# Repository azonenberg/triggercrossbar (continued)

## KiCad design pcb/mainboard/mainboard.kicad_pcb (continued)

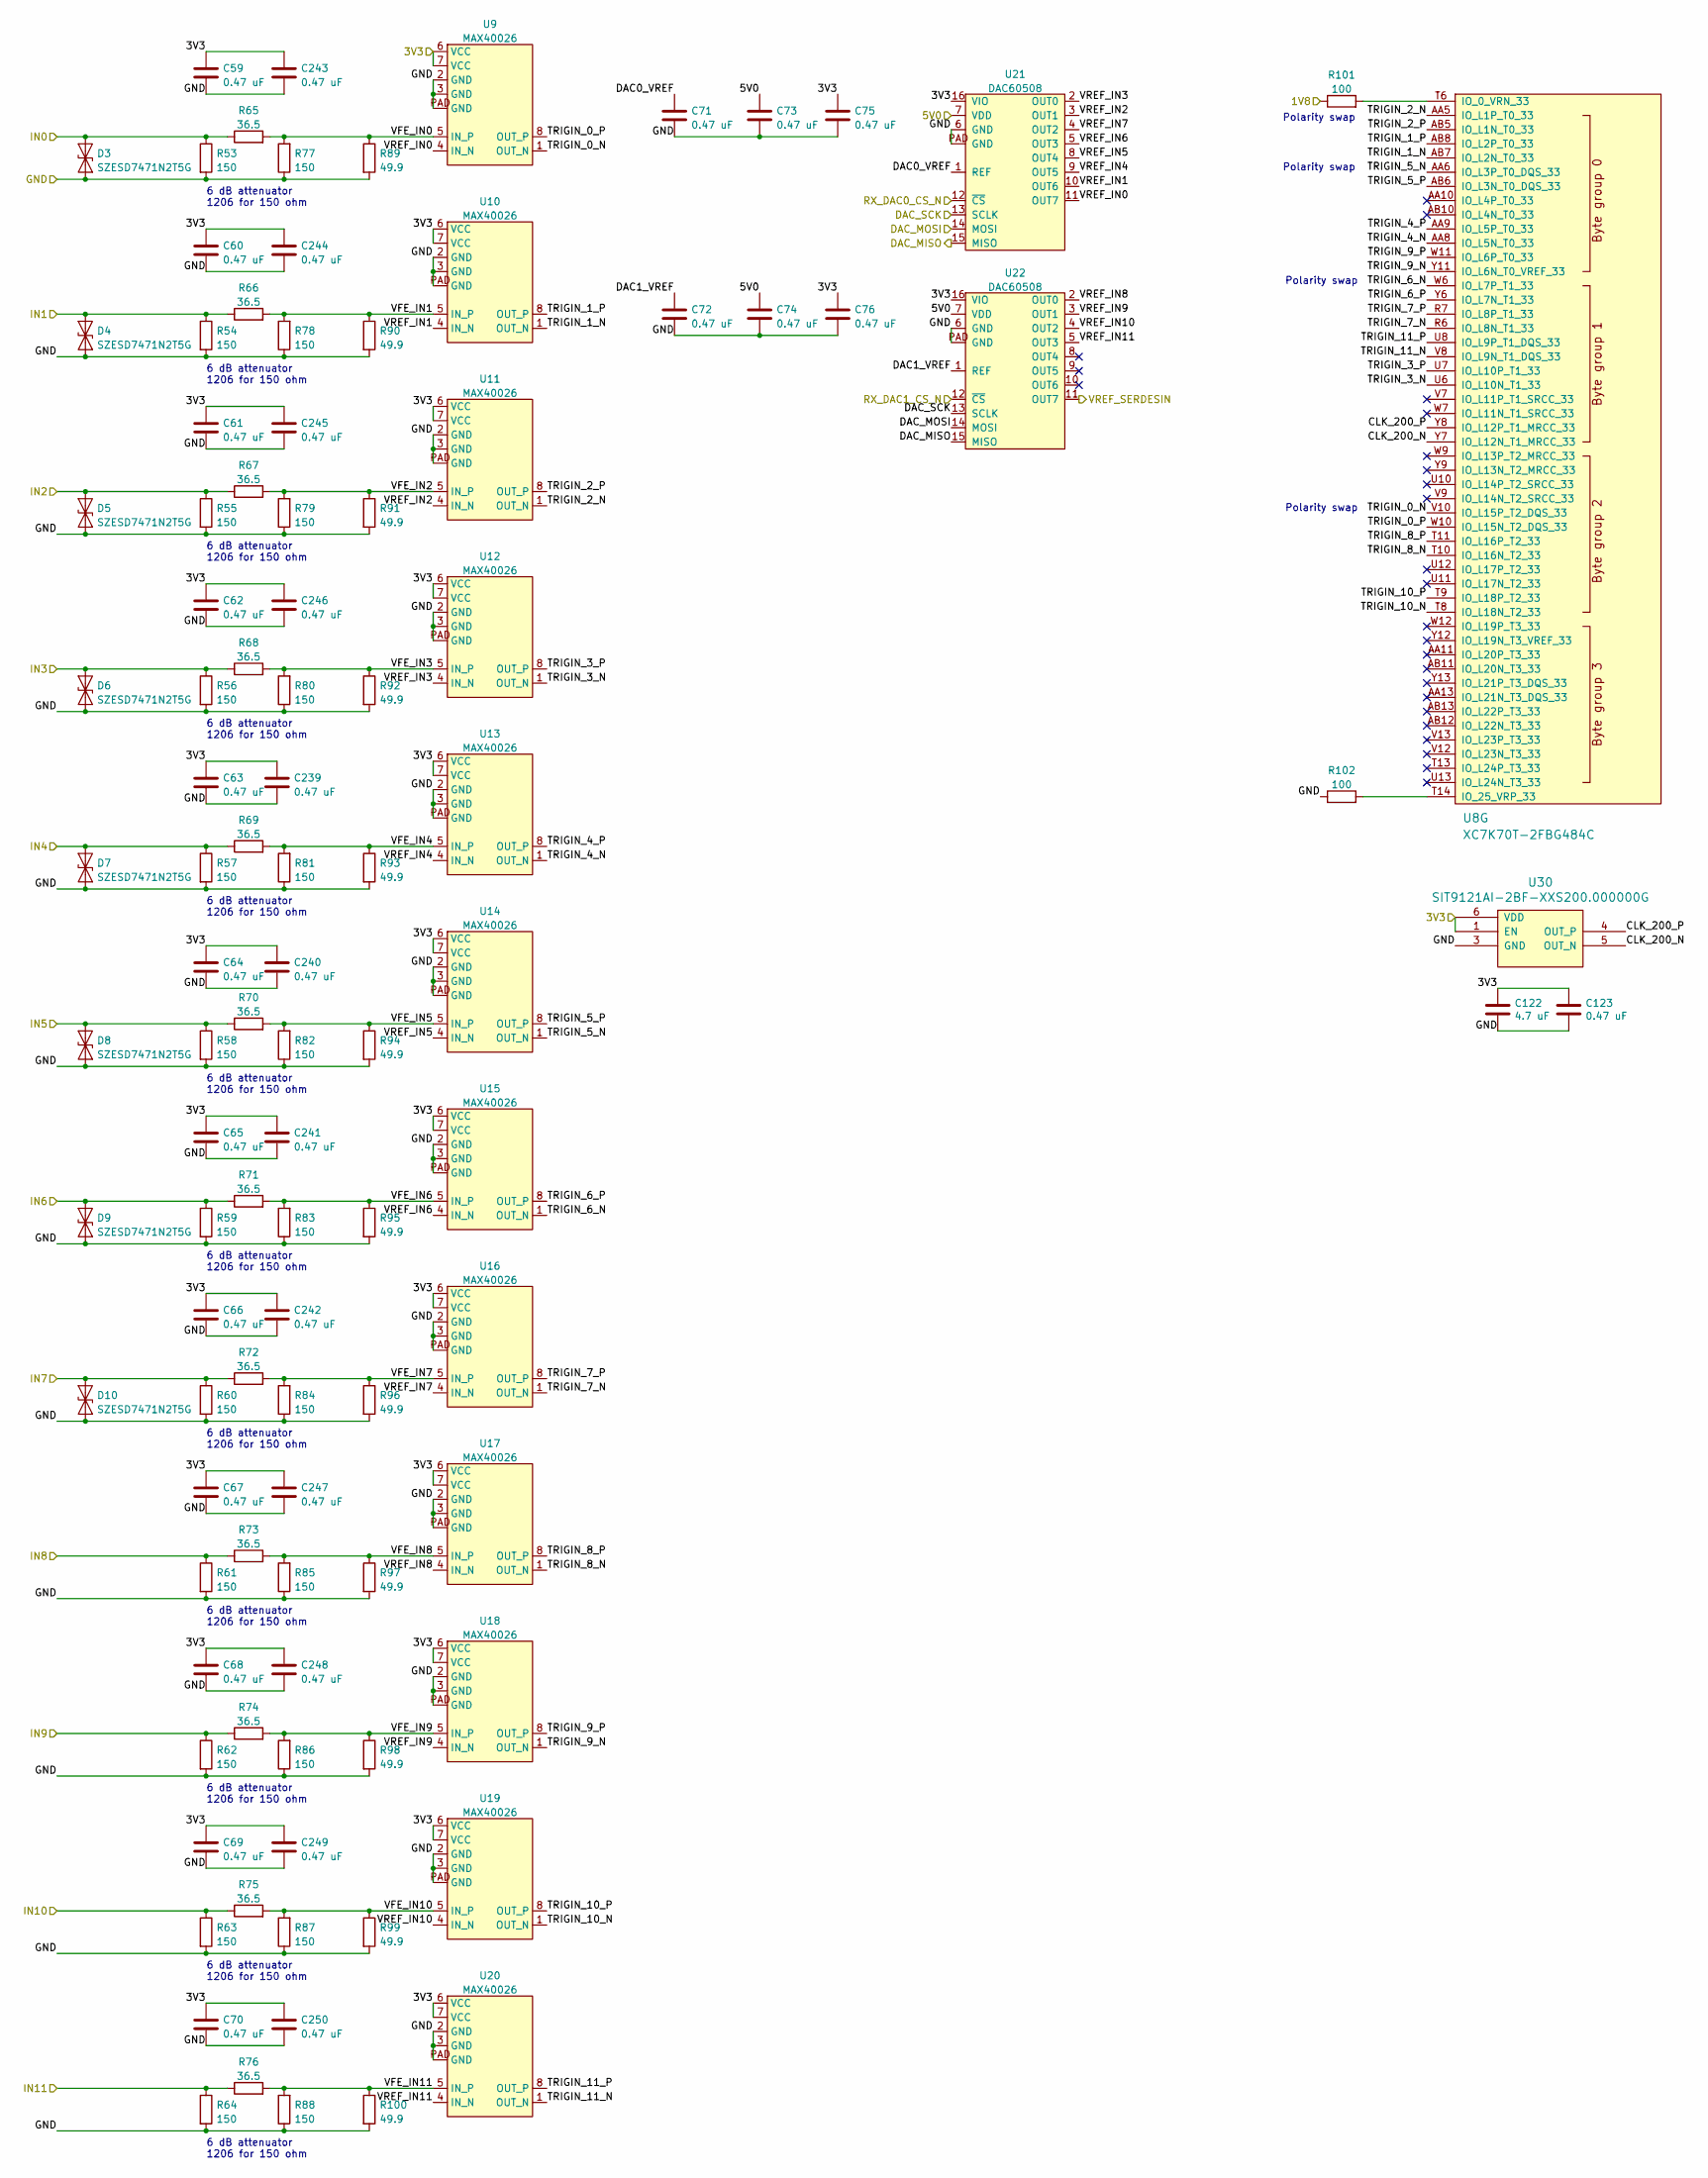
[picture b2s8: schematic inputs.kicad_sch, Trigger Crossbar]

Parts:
C59, C60, C61, C62, C63, C64, C65, C66, C67, C68, C69, C70, C71, C72, C73, C74, C75, C76, C123, C239, C240, C241, C242, C243, C244, C245, C246, C247, C248, C249, C250: 0.47 uF; EIA_0402_CAP_NOSILK
C122: 4.7 uF; EIA_0603_CAP_NOSILK
D3, D4, D5, D6, D7, D8, D9, D10: SZESD7471N2T5G; SOD882
R53, R54, R55, R56, R57, R58, R59, R60, R61, R62, R63, R64, R77, R78, R79, R80, R81, R82, R83, R84, R85, R86, R87, R88: 150; EIA_1206_CAP_NOSILK
R65, R66, R67, R68, R69, R70, R71, R72, R73, R74, R75, R76: 36.5; EIA_0402_RES_NOSILK
R89, R90, R91, R92, R93, R94, R95, R96, R97, R98, R99, R100: 49.9; EIA_0402_RES_NOSILK
R101, R102: 100; EIA_0402_RES_NOSILK
U8: XC7K70T-2FBG484C; BGA_484_22x22_FULLARRAY_1MM
U9, U10, U11, U12, U13, U14, U15, U16, U17, U18, U19, U20: MAX40026; DFN_8_0.5MM_2x2MM
U21, U22: DAC60508; QFN_16_0.5MM_3x3MM
U30: SIT9121AI-2BF-XXS200.000000G; OSCILLATOR_LVDS_3.2x2.5

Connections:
/3V3: C59.1, C60.1, C61.1, C62.1, C63.1, C64.1, C65.1, C66.1, C67.1, C68.1, C69.1, C70.1, C75.1, C76.1, C122.1, C123.1, C239.1, C240.1, C241.1, C242.1, C243.1, C244.1, C245.1, C246.1, C247.1, C248.1, C249.1, C250.1, U9.6 (VCC), U9.7 (VCC), U10.6 (VCC), U10.7 (VCC), U11.6 (VCC), U11.7 (VCC), U12.6 (VCC), U12.7 (VCC), U13.6 (VCC), U13.7 (VCC), U14.6 (VCC), U14.7 (VCC), U15.6 (VCC), U15.7 (VCC), U16.6 (VCC), U16.7 (VCC), U17.6 (VCC), U17.7 (VCC), U18.6 (VCC), U18.7 (VCC), U19.6 (VCC), U19.7 (VCC), U20.6 (VCC), U20.7 (VCC), U21.16 (VIO), U22.16 (VIO), U30.1 (EN), U30.6 (VDD); also elsewhere on the board
/5V0: C73.1, C74.1, U21.7 (VDD), U22.7 (VDD); also elsewhere on the board
/Connectors/IN0: D3.2 (A2), R53.1, R65.1; also elsewhere on the board
/Connectors/IN1: D4.2 (A2), R54.1, R66.1; also elsewhere on the board
/Connectors/IN2: D5.2 (A2), R55.1, R67.1; also elsewhere on the board
/Connectors/IN3: D6.2 (A2), R56.1, R68.1; also elsewhere on the board
/Connectors/IN4: D7.2 (A2), R57.1, R69.1; also elsewhere on the board
/Connectors/IN5: D8.2 (A2), R58.1, R70.1; also elsewhere on the board
/Connectors/IN6: D9.2 (A2), R59.1, R71.1; also elsewhere on the board
/Connectors/IN7: D10.2 (A2), R60.1, R72.1; also elsewhere on the board
/Connectors/IN8: R61.1, R73.1; also elsewhere on the board
/Connectors/IN9: R62.1, R74.1; also elsewhere on the board
/Connectors/IN10: R63.1, R75.1; also elsewhere on the board
/Connectors/IN11: R64.1, R76.1; also elsewhere on the board
/DAC_MISO: U21.15 (MISO), U22.15 (MISO); also elsewhere on the board
/DAC_MOSI: U21.14 (MOSI), U22.14 (MOSI); also elsewhere on the board
/DAC_SCK: U21.13 (SCLK), U22.13 (SCLK); also elsewhere on the board
/GND: C59.2, C60.2, C61.2, C62.2, C63.2, C64.2, C65.2, C66.2, C67.2, C68.2, C69.2, C70.2, C71.2, C72.2, C73.2, C74.2, C75.2, C76.2, C122.2, C123.2, C239.2, C240.2, C241.2, C242.2, C243.2, C244.2, C245.2, C246.2, C247.2, C248.2, C249.2, C250.2, D3.1 (A1), D4.1 (A1), D5.1 (A1), D6.1 (A1), D7.1 (A1), D8.1 (A1), D9.1 (A1), D10.1 (A1), R53.2, R54.2, R55.2, R56.2, R57.2, R58.2, R59.2, R60.2, R61.2, R62.2, R63.2, R64.2, R77.1, R78.1, R79.1, R80.1, R81.1, R82.1, R83.1, R84.1, R85.1, R86.1, R87.1, R88.1, R89.2, R90.2, R91.2, R92.2, R93.2, R94.2, R95.2, R96.2, R97.2, R98.2, R99.2, R100.2, R102.1, U9.2 (GND), U9.3 (GND), U9.PAD (GND), U10.2 (GND), U10.3 (GND), U10.PAD (GND), U11.2 (GND), U11.3 (GND), U11.PAD (GND), U12.2 (GND), U12.3 (GND), U12.PAD (GND), U13.2 (GND), U13.3 (GND), U13.PAD (GND), U14.2 (GND), U14.3 (GND), U14.PAD (GND), U15.2 (GND), U15.3 (GND), U15.PAD (GND), U16.2 (GND), U16.3 (GND), U16.PAD (GND), U17.2 (GND), U17.3 (GND), U17.PAD (GND), U18.2 (GND), U18.3 (GND), U18.PAD (GND), U19.2 (GND), U19.3 (GND), U19.PAD (GND), U20.2 (GND), U20.3 (GND), U20.PAD (GND), U21.6 (GND), U21.PAD (GND), U22.6 (GND), U22.PAD (GND), U30.3 (GND); also elsewhere on the board
/Inputs/CLK_200_N: U8.Y7 (IO_L12N_T1_MRCC_33), U30.5 (OUT_N)
/Inputs/CLK_200_P: U8.Y8 (IO_L12P_T1_MRCC_33), U30.4 (OUT_P)
/Inputs/DAC0_VREF: C71.1, U21.1 (REF)
/Inputs/DAC1_VREF: C72.1, U22.1 (REF)
/Inputs/TRIGIN_0_N: U8.V10 (IO_L15P_T2_DQS_33), U9.1 (OUT_N)
/Inputs/TRIGIN_0_P: U8.W10 (IO_L15N_T2_DQS_33), U9.8 (OUT_P)
/Inputs/TRIGIN_1_N: U8.AB7 (IO_L2N_T0_33), U10.1 (OUT_N)
/Inputs/TRIGIN_1_P: U8.AB8 (IO_L2P_T0_33), U10.8 (OUT_P)
/Inputs/TRIGIN_2_N: U8.AA5 (IO_L1P_T0_33), U11.1 (OUT_N)
/Inputs/TRIGIN_2_P: U8.AB5 (IO_L1N_T0_33), U11.8 (OUT_P)
/Inputs/TRIGIN_3_N: U8.U6 (IO_L10N_T1_33), U12.1 (OUT_N)
/Inputs/TRIGIN_3_P: U8.U7 (IO_L10P_T1_33), U12.8 (OUT_P)
/Inputs/TRIGIN_4_N: U8.AA8 (IO_L5N_T0_33), U13.1 (OUT_N)
/Inputs/TRIGIN_4_P: U8.AA9 (IO_L5P_T0_33), U13.8 (OUT_P)
/Inputs/TRIGIN_5_N: U8.AA6 (IO_L3P_T0_DQS_33), U14.1 (OUT_N)
/Inputs/TRIGIN_5_P: U8.AB6 (IO_L3N_T0_DQS_33), U14.8 (OUT_P)
/Inputs/TRIGIN_6_N: U8.W6 (IO_L7P_T1_33), U15.1 (OUT_N)
/Inputs/TRIGIN_6_P: U8.Y6 (IO_L7N_T1_33), U15.8 (OUT_P)
/Inputs/TRIGIN_7_N: U8.R6 (IO_L8N_T1_33), U16.1 (OUT_N)
/Inputs/TRIGIN_7_P: U8.R7 (IO_L8P_T1_33), U16.8 (OUT_P)
/Inputs/TRIGIN_8_N: U8.T10 (IO_L16N_T2_33), U17.1 (OUT_N)
/Inputs/TRIGIN_8_P: U8.T11 (IO_L16P_T2_33), U17.8 (OUT_P)
/Inputs/TRIGIN_9_N: U8.Y11 (IO_L6N_T0_VREF_33), U18.1 (OUT_N)
/Inputs/TRIGIN_9_P: U8.W11 (IO_L6P_T0_33), U18.8 (OUT_P)
/Inputs/TRIGIN_10_N: U8.T8 (IO_L18N_T2_33), U19.1 (OUT_N)
/Inputs/TRIGIN_10_P: U8.T9 (IO_L18P_T2_33), U19.8 (OUT_P)
/Inputs/TRIGIN_11_N: U8.V8 (IO_L9N_T1_DQS_33), U20.1 (OUT_N)
/Inputs/TRIGIN_11_P: U8.U8 (IO_L9P_T1_DQS_33), U20.8 (OUT_P)
/Inputs/VFE_IN0: R65.2, R77.2, R89.1, U9.5 (IN_P)
/Inputs/VFE_IN1: R66.2, R78.2, R90.1, U10.5 (IN_P)
/Inputs/VFE_IN2: R67.2, R79.2, R91.1, U11.5 (IN_P)
/Inputs/VFE_IN3: R68.2, R80.2, R92.1, U12.5 (IN_P)
/Inputs/VFE_IN4: R69.2, R81.2, R93.1, U13.5 (IN_P)
/Inputs/VFE_IN5: R70.2, R82.2, R94.1, U14.5 (IN_P)
/Inputs/VFE_IN6: R71.2, R83.2, R95.1, U15.5 (IN_P)
/Inputs/VFE_IN7: R72.2, R84.2, R96.1, U16.5 (IN_P)
/Inputs/VFE_IN8: R73.2, R85.2, R97.1, U17.5 (IN_P)
/Inputs/VFE_IN9: R74.2, R86.2, R98.1, U18.5 (IN_P)
/Inputs/VFE_IN10: R75.2, R87.2, R99.1, U19.5 (IN_P)
/Inputs/VFE_IN11: R76.2, R88.2, R100.1, U20.5 (IN_P)
/Inputs/VREF_IN0: U9.4 (IN_N), U21.11 (OUT7)
/Inputs/VREF_IN1: U10.4 (IN_N), U21.10 (OUT6)
/Inputs/VREF_IN2: U11.4 (IN_N), U21.3 (OUT1)
/Inputs/VREF_IN3: U12.4 (IN_N), U21.2 (OUT0)
/Inputs/VREF_IN4: U13.4 (IN_N), U21.9 (OUT5)
/Inputs/VREF_IN5: U14.4 (IN_N), U21.8 (OUT4)
/Inputs/VREF_IN6: U15.4 (IN_N), U21.5 (OUT3)
/Inputs/VREF_IN7: U16.4 (IN_N), U21.4 (OUT2)
/Inputs/VREF_IN8: U17.4 (IN_N), U22.2 (OUT0)
/Inputs/VREF_IN9: U18.4 (IN_N), U22.3 (OUT1)
/Inputs/VREF_IN10: U19.4 (IN_N), U22.4 (OUT2)
/Inputs/VREF_IN11: U20.4 (IN_N), U22.5 (OUT3)
/Management/RX_DAC0_CS_N: U21.12 (~CS); also elsewhere on the board
/Management/RX_DAC1_CS_N: U22.12 (~CS); also elsewhere on the board
/VREF_SERDESIN: U22.11 (OUT7); also elsewhere on the board
unnamed: R101.2, U8.T6 (IO_0_VRN_33)
unnamed: R102.2, U8.T14 (IO_25_VRP_33)

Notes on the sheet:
6 dB attenuator 1206 for 150 ohm
Polarity swap

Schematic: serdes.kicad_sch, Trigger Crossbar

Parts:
C53, C54, C57, C58, C116, C117, C118, C119, C120, C121: 0.1 uF; EIA_0402_CAP_NOSILK
C55, C56: 22 uF; EIA_0805_CAP_NOSILK
C114, C115: 0.47 uF; EIA_0402_CAP_NOSILK
C221, C222, C223, C230, C231: 4.7 uF; EIA_0603_CAP_NOSILK
C224, C225, C226, C232, C233: 330 pF; EIA_0402_CAP_NOSILK
C227, C228, C229, C234, C235: 100 pF; EIA_0402_CAP_NOSILK
D20, D21, D22, D23, D24, D25, D26, D27, D28, D29, D30: SZESD7471N2T5G; SOD882
J6: CONN_SFP_HOST; CONN_SFP+_AMPHENOL_UE76_A10_2000T
J7: SFP_CAGE; CONN_SFP_CAGE_TE_2007194-1
J16, J17, J18, J19, J20, J21, J22, J23, J24, J25, J26: SMPM; CONN_SMPM_AMPHENOL_C925-197J-51PT
L1, L2: 4.7 uH; EIA_0805_INDUCTOR_NOSILK
R47: 100; EIA_0402_RES_NOSILK
R48: 0.1; EIA_0402_RES_NOSILK
R49, R50: 0.5; EIA_0402_RES_NOSILK
R51, R52: 4.7K; EIA_0402_RES_NOSILK
R121, R122, R123: DNP; EIA_0402_RES_NOSILK
R161, R162: 1K; EIA_0402_RES_NOSILK
U8: XC7K70T-2FBG484C; BGA_484_22x22_FULLARRAY_1MM
U27: SIT9121AI-2BF-XXS200.000000G; OSCILLATOR_LVDS_3.2x2.5
U28: SIT9121AI-2BF-XXS156.250000G; OSCILLATOR_LVDS_3.2x2.5
U29: HMC675LP3E; QFN_16_0.5MM_3x3MM

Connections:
/1V2: C222.1, C225.1, C228.1, C231.1, C233.1, C235.1, U29.9 (VCCO), U29.12 (VCCO); also elsewhere on the board
/3V0_N: C223.1, C226.1, C229.1, U29.13 (VEE), U29.PAD (VEE); also elsewhere on the board
/3V3: C114.1, C115.1, C221.1, C224.1, C227.1, C230.1, C232.1, C234.1, R48.2, R51.2, R52.2, R121.1, R161.1, R162.1, U27.1 (EN), U27.6 (VDD), U28.1 (EN), U28.6 (VDD), U29.5 (VCCI), U29.16 (VCCI); also elsewhere on the board
/GND: C53.2, C54.2, C57.2, C58.2, C114.2, C115.2, C221.2, C222.2, C223.2, C224.2, C225.2, C226.2, C227.2, C228.2, C229.2, C230.2, C231.2, C232.2, C233.2, C234.2, C235.2, D20.1 (A1), D21.1 (A1), D22.1 (A1), D23.1 (A1), D24.1 (A1), D25.1 (A1), D26.1 (A1), D27.1 (A1), D28.1 (A1), D29.1 (A1), D30.1 (A1), J6.1 (GND_TX), J6.10 (GND_RX), J6.11 (GND_RX), J6.14 (GND_RX), J6.17 (GND_TX), J6.20 (GND_TX), J7.1, J16.2 (Ext), J17.2 (Ext), J18.2 (Ext), J19.2 (Ext), J20.2 (Ext), J21.2 (Ext), J22.2 (Ext), J23.2 (Ext), J24.2 (Ext), J25.2 (Ext), J26.2 (Ext), R49.1, R50.1, R122.1, R123.2, U27.3 (GND), U28.3 (GND), U29.1 (VTP), U29.8 (NC/GND), U29.15 (RTN); also elsewhere on the board
/Management/SFP_MOD_ABS: J6.6 (MOD_ABS); also elsewhere on the board
/Management/SFP_RX_LOS: J6.8 (RX_LOS); also elsewhere on the board
/Management/SFP_TX_DISABLE: J6.3 (TX_DISABLE); also elsewhere on the board
/Management/SFP_TX_FAULT: J6.2 (TX_FAULT); also elsewhere on the board
/Transceivers/BERT_RX0_N: D27.2 (A2), J23.1 (In), U8.B5 (GTX_RX_3_N)
/Transceivers/BERT_RX0_P: D26.2 (A2), J22.1 (In), U8.B6 (GTX_RX_3_P)
/Transceivers/BERT_RX1_N: D25.2 (A2), J21.1 (In), U8.C3 (GTX_RX_2_N)
/Transceivers/BERT_RX1_P: D24.2 (A2), J20.1 (In), U8.C4 (GTX_RX_2_P)
/Transceivers/BERT_TX0_N: D23.2 (A2), J19.1 (In), U8.A3 (GTX_TX_3_N)
/Transceivers/BERT_TX0_P: D22.2 (A2), J18.1 (In), U8.A4 (GTX_TX_3_P)
/Transceivers/BERT_TX1_N: D21.2 (A2), J17.1 (In), U8.B1 (GTX_TX_2_N)
/Transceivers/BERT_TX1_P: D20.2 (A2), J16.1 (In), U8.B2 (GTX_TX_2_P)
/Transceivers/CDRTRIG_IN: D28.2 (A2), J24.1 (In), U29.2 (IN_P)
/Transceivers/CDRTRIG_RX_AC_N: C121.1, U29.10 (Q_N)
/Transceivers/CDRTRIG_RX_AC_P: C120.1, U29.11 (Q_P)
/Transceivers/CDRTRIG_RX_N: C121.2, U8.E3 (GTX_RX_1_N)
/Transceivers/CDRTRIG_RX_P: C120.2, U8.E4 (GTX_RX_1_P)
/Transceivers/FASTSYNC_TX_N: D30.2 (A2), J26.1 (In), U8.D1 (GTX_TX_1_N)
/Transceivers/FASTSYNC_TX_P: D29.2 (A2), J25.1 (In), U8.D2 (GTX_TX_1_P)
/Transceivers/GTC1_N: C117.1, U27.5 (OUT_N)
/Transceivers/GTC1_P: C116.1, U27.4 (OUT_P)
/Transceivers/GTC2_N: C119.1, U28.5 (OUT_N)
/Transceivers/GTC2_P: C118.1, U28.4 (OUT_P)
/Transceivers/GTX_REFCLK_156M25_N: C119.2, U8.D5 (GTX_REFCLK_0_N)
/Transceivers/GTX_REFCLK_156M25_P: C118.2, U8.D6 (GTX_REFCLK_0_P)
/Transceivers/GTX_REFCLK_SPARE_N: C117.2, U8.F5 (GTX_REFCLK_1_N)
/Transceivers/GTX_REFCLK_SPARE_P: C116.2, U8.F6 (GTX_REFCLK_1_P)
/Transceivers/SFP_3V3: C53.1, C54.1, L1.2, L2.2, R48.1
/Transceivers/SFP_I2C_SCL: J6.5 (SCL), R52.1; also elsewhere on the board
/Transceivers/SFP_I2C_SDA: J6.4 (SDA), R51.1; also elsewhere on the board
/Transceivers/SFP_RS0: J6.7 (RS0), R161.2
/Transceivers/SFP_RS1: J6.9 (RS1), R162.2
/Transceivers/SFP_RX_N: J6.12 (RX_N), U8.G3 (GTX_RX_0_N)
/Transceivers/SFP_RX_P: J6.13 (RX_P), U8.G4 (GTX_RX_0_P)
/Transceivers/SFP_TX_N: J6.19 (TX_N), U8.F2 (GTX_TX_0_P)
/Transceivers/SFP_TX_P: J6.18 (TX_P), U8.F1 (GTX_TX_0_N)
/Transceivers/SFP_VDD_RX: C55.1, C57.1, J6.15 (VDD_RX), L1.1
/Transceivers/SFP_VDD_TX: C56.1, C58.1, J6.16 (VDD_TX), L2.1
/VREF_SERDESIN: U29.3 (IN_N); also elsewhere on the board
unnamed: C55.2, R49.2
unnamed: C56.2, R50.2
unnamed: R47.1, U8.H2 (GTX_RREF)
unnamed: R47.2, U8.H1 (GTX_VTTRCAL)
unnamed: R121.2, U29.6 (LE_N)
unnamed: R122.2, U29.7 (LE_P)
unnamed: R123.1, U29.4 (VTN)

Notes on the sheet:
Can use 156.25 for both Provide a second oscillator footprint just in case
Pair swap for routing
SFP+ power filtering
Single ended CDR trigger input

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
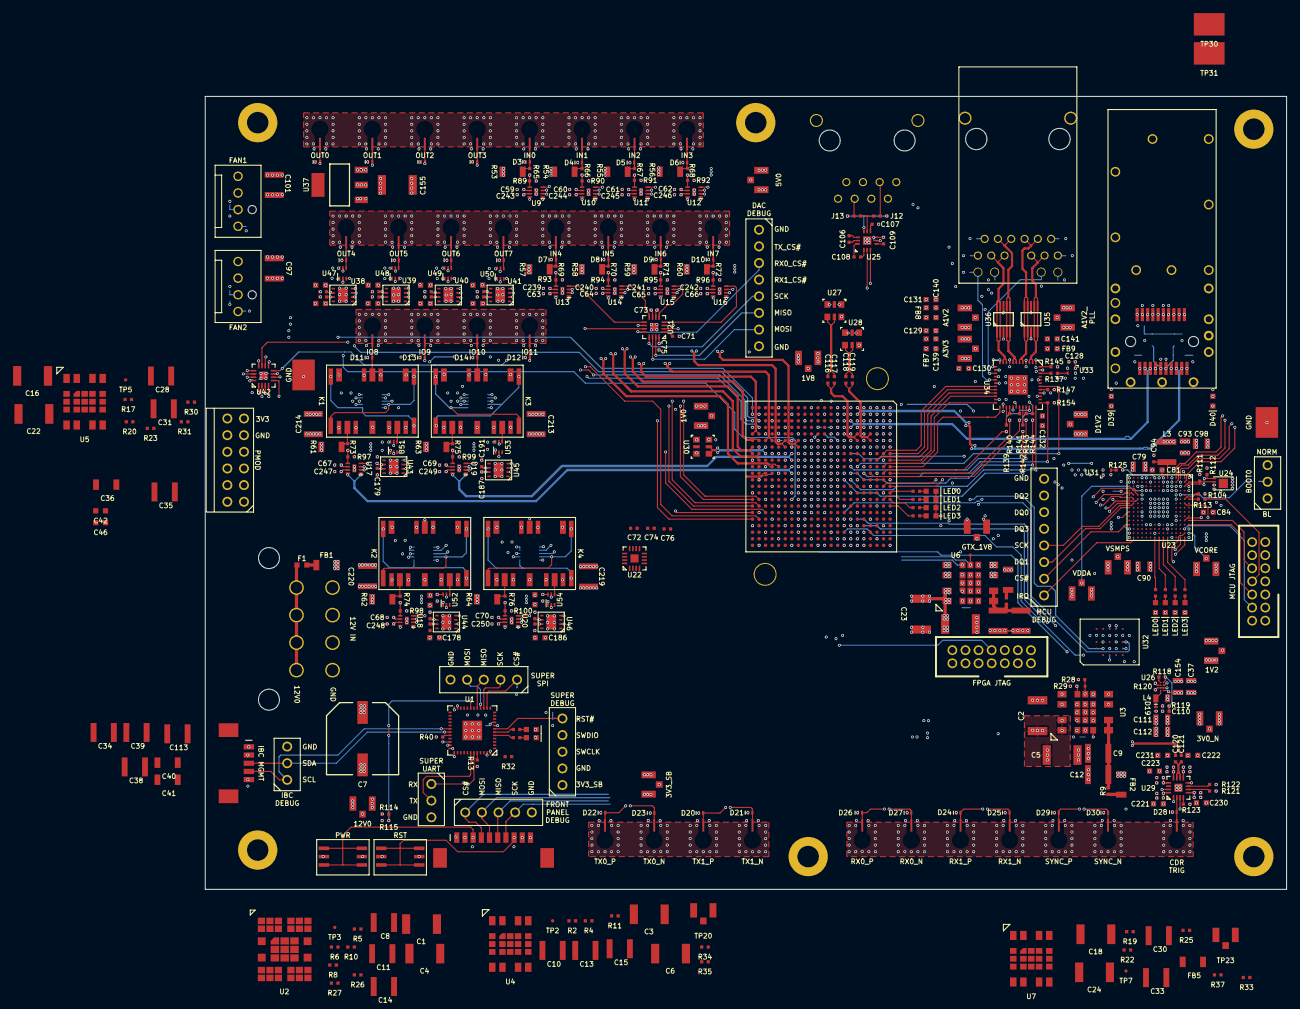
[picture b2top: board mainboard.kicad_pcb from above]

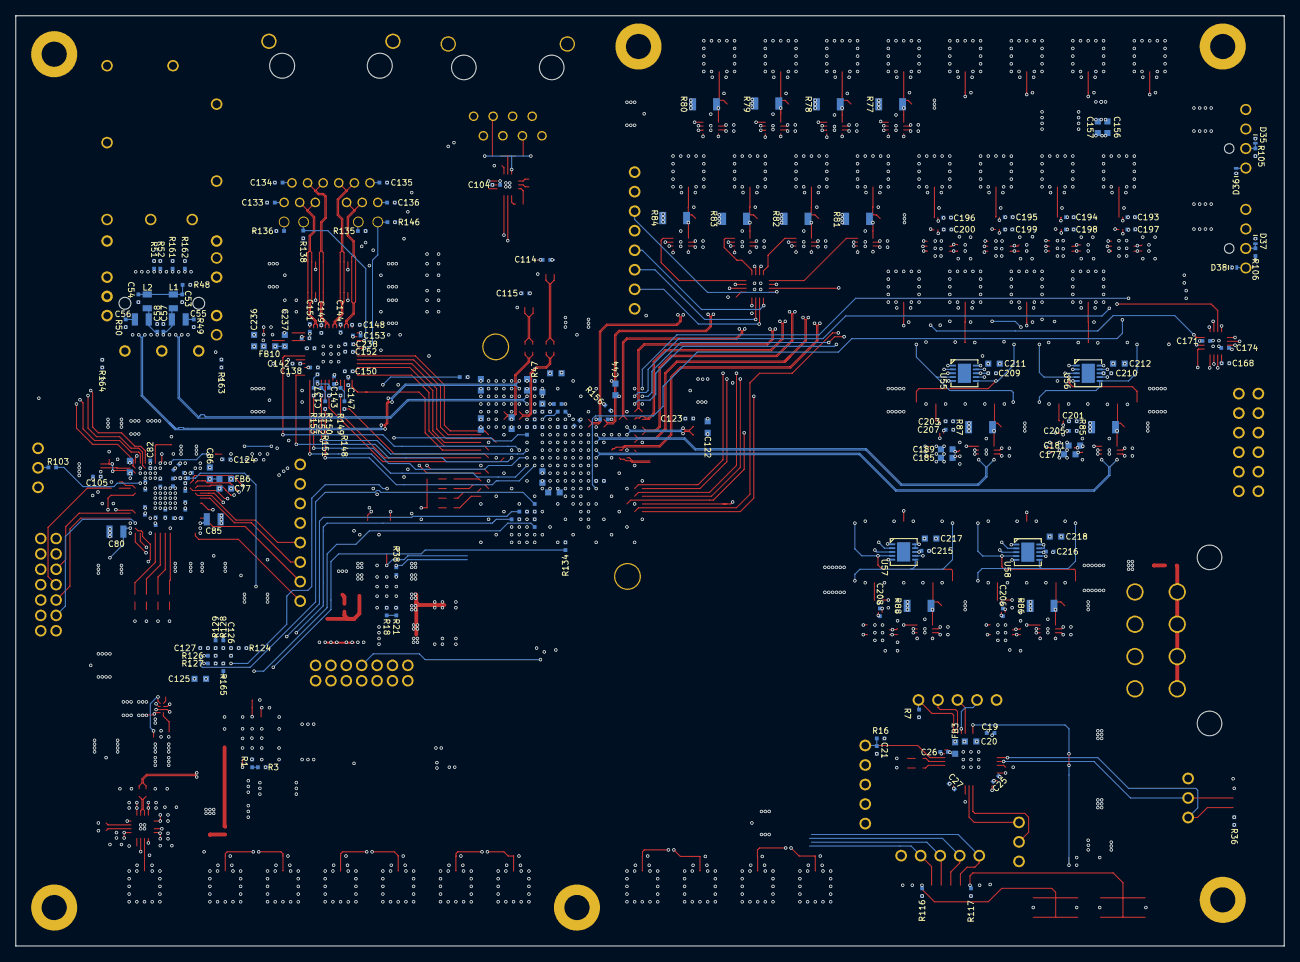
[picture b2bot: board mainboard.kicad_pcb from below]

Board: 10 copper layers, 165.0 x 121.0 mm, 629 parts (182 on the bottom side), 396 nets.

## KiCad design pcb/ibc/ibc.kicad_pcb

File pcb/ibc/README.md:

# Intermediate Bus Converter

This board takes in 48V DC from an external supply on a 6-pin Molex Mini-Fit Jr connector (p/n 0039291067).

Initial development will be using bench supplies and a Mean Well GST280A48-C6P however the system is intended to support
rack or lab wide DC bus architectures as well.

# Output specs

12V DC at up to 6A (72W)

Expected efficiency at 48 -> 12V is 93%
So for 72W out we will draw 77.4W in (1.61A) and dissipate 5.4W in the converter.

# Monitoring subsystem

TPS7A2533DRVR 3.3V LDO driven from 12V output

300 mA spec, but target << 1W dissipation
With 12V -> 3.3V we drop 8.7V so we'll hit 1W at only 115 mA

## Connector

Management header to main logic board:
* 3.3V standby LDO rail (thermally limited to 115 mA, aim for much less)
* I2C bus with MCU and temp sensor
* 3.3V active high enable for main 12V rail
* Ground

Molex PicoBlade 1.25mm
	Cable P/N 0151340501 (100mm)
	Connector P/N 532610571

## Interface

Management protocol TODO

## Sensors

AT30TS74 temperature sensor (at least one, possibly two)

AD8218 current shunt monitor on input and output rails

Internal STM32L031 ADC is 12 bits

### Input shunt

25 milliohms gives 500 mV/A, so 805 mV full scale range. At 1.61A will dissipate 80.5 mW

### Input voltage divider

30:1 divider gives 1.6V nominal

### Output shunt

5 milliohms gives 100 mV/A so 800 mV full scale range. At 8A will dissipate 320 mW

### Output voltage divider

5:1 divider gives 2.4V nominal

# General design notes

Cout 200 to 1200 uF. Put 330 uF in the module

STM32L031 (package TBD)

Soft start load switch on the main 12V rail, driving into additional bulk cap

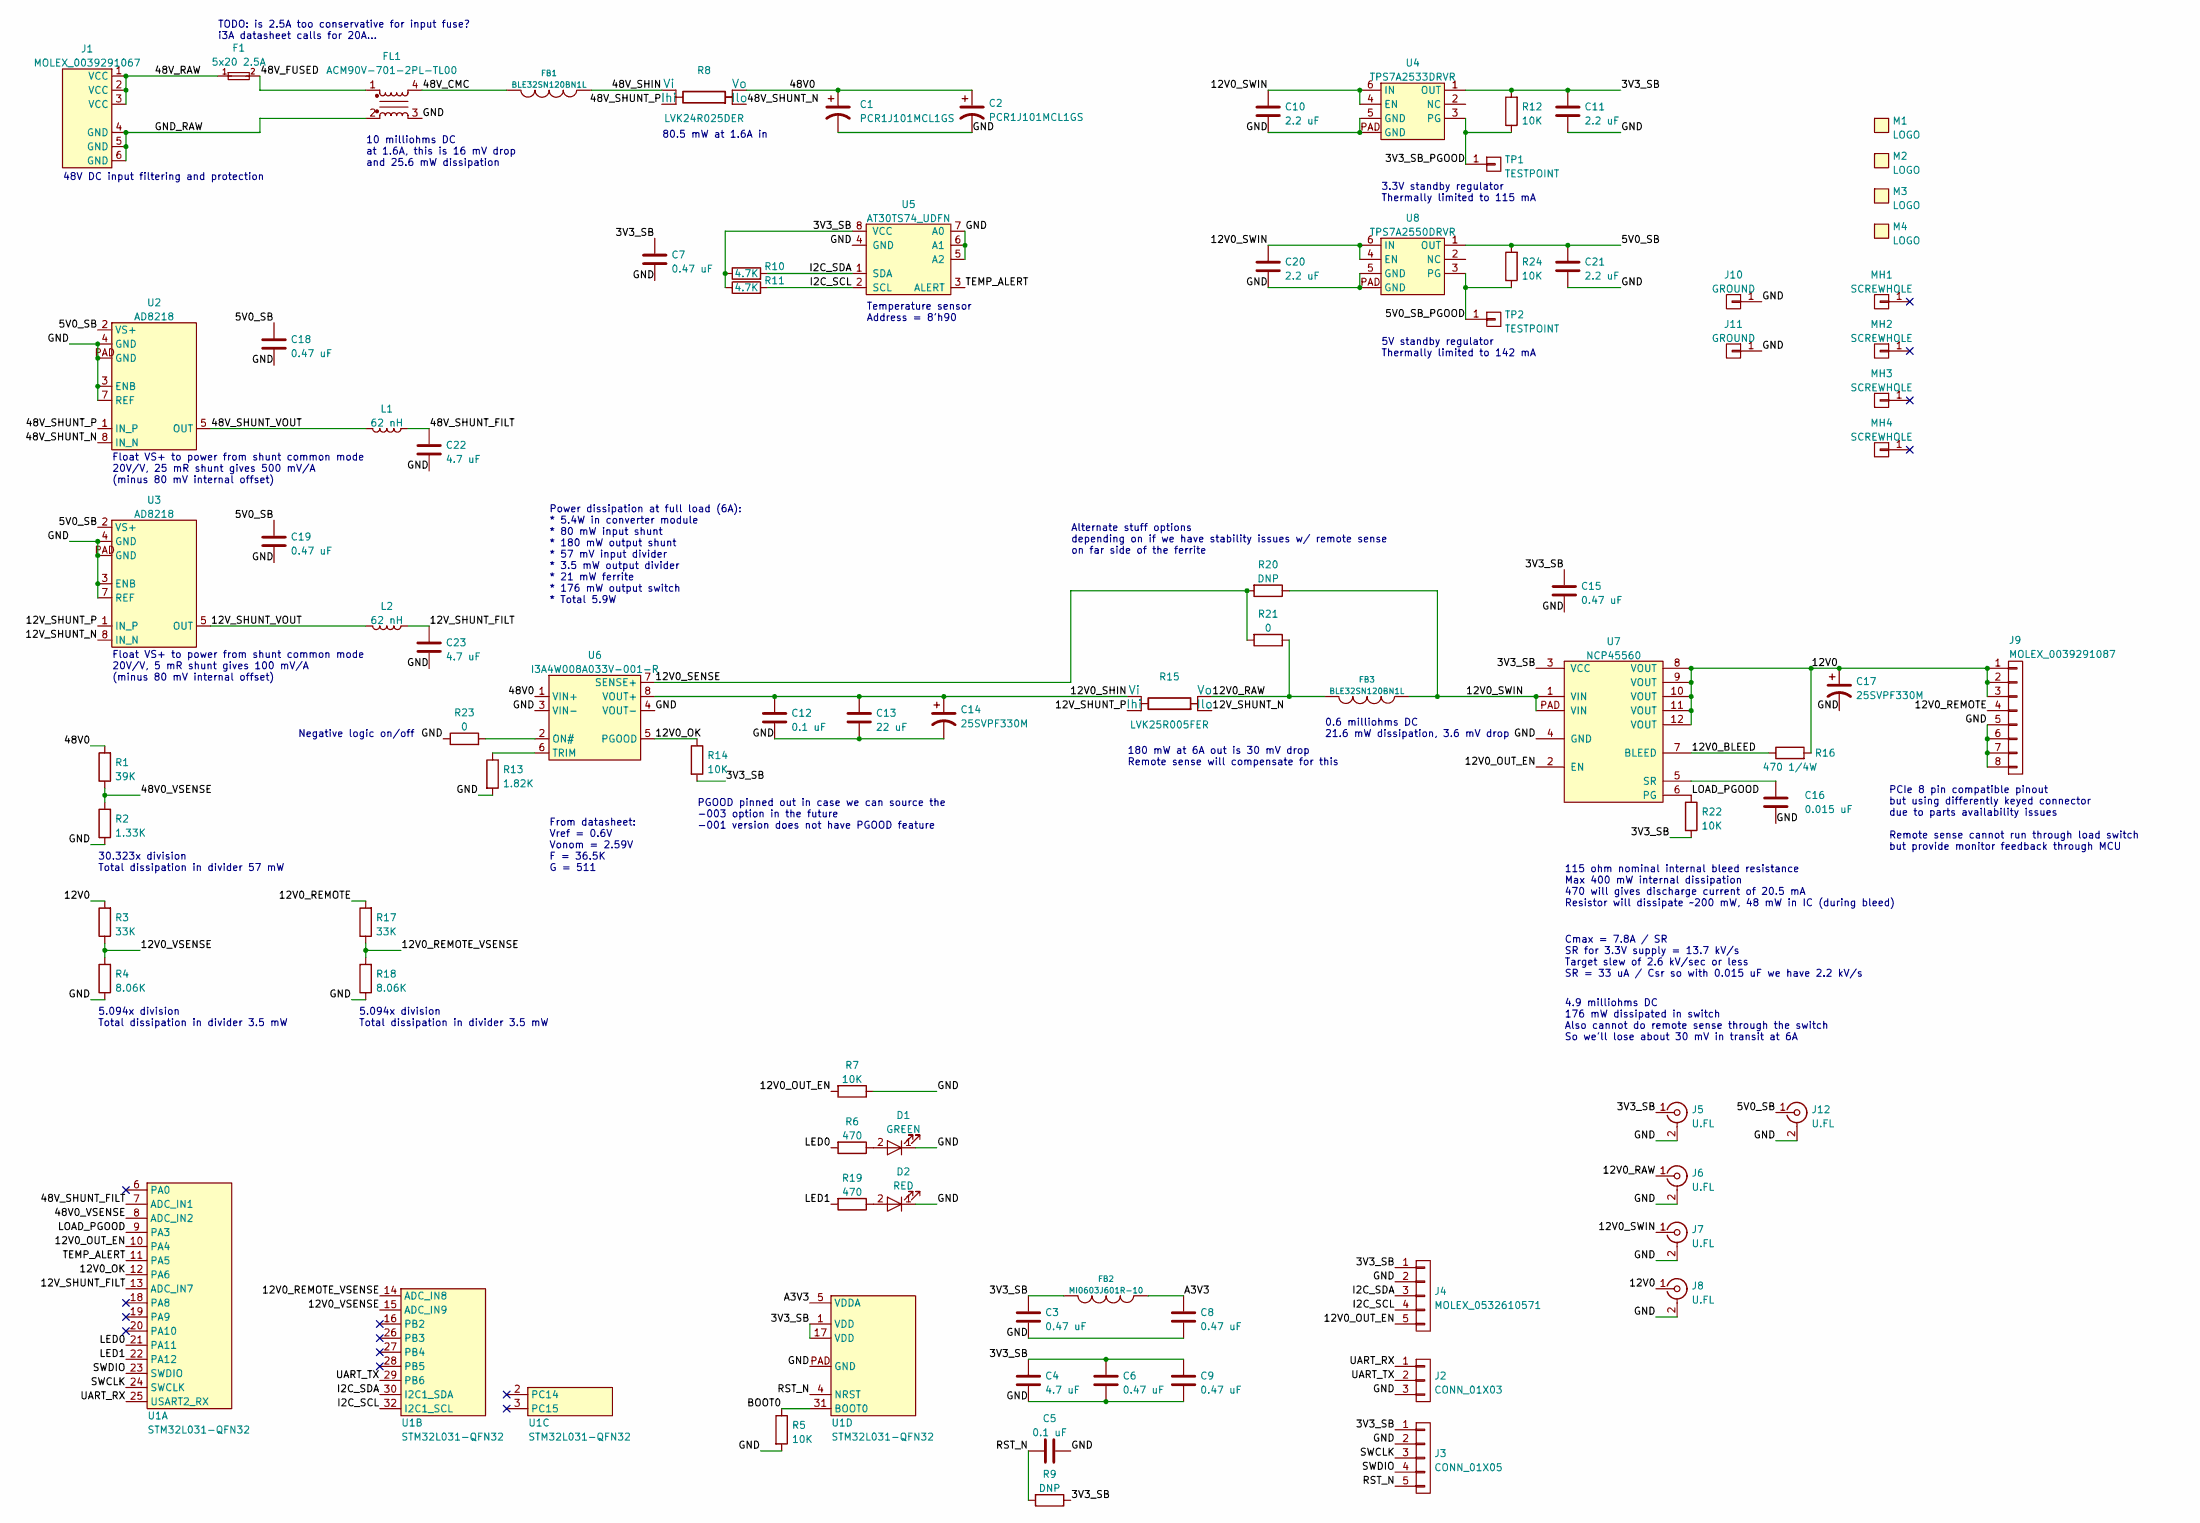
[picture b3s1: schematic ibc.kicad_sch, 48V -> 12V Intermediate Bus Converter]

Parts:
C1, C2: PCR1J101MCL1GS; CAP_AL_10MM_SMT
C3, C6, C7, C8, C9, C15, C18, C19: 0.47 uF; EIA_0402_CAP_NOSILK
C4, C22, C23: 4.7 uF; EIA_0603_CAP_NOSILK
C5: 0.1 uF; EIA_0402_CAP_NOSILK
C10, C11, C20, C21: 2.2 uF; EIA_0805_CAP_NOSILK
C12: 0.1 uF; EIA_1206_CAP_NOSILK
C13: 22 uF; EIA_1812_CAP_NOSILK
C14, C17: 25SVPF330M; CAP_AL_10MM_SMT
C16: 0.015 uF; EIA_0603_CAP_NOSILK
D1: GREEN; EIA_0603_LED
D2: RED; EIA_0603_LED
F1: 5x20 2.5A; FUSEHOLDER_KEYSTONE_4527
FB1, FB3: BLE32SN120BN1L; EIA_1210_CAP_NOSILK
FB2: MI0603J601R-10; EIA_0603_INDUCTOR_NOSILK
FL1: ACM90V-701-2PL-TL00; CMC_TDK_ACM90V
J1: MOLEX_0039291067; CONN_MOLEX_MINIFITJR_6POS_0039291067
J2: CONN_01X03; CONN_HEADER_2.54MM_1x3
J3: CONN_01X05; CONN_HEADER_2.54MM_1x5
J4: MOLEX_0532610571; CONN_MOLEX_PICOBLADE_5POS_0532610571
J5, J6, J7, J8, J12: U.FL; CONN_U.FL_TE_1909763-1
J9: MOLEX_0039291087; CONN_MOLEX_MINIFITJR_8POS_0039291087
J10, J11: GROUND; TESTPOINT_SMT_KEYSTONE_5016
L1, L2: 62 nH; EIA_0402_CAP_NOSILK
M1: LOGO; LONGTHING-1200DPI
M2: LOGO; Logo_silk_OSHW_6x6mm
M3: LOGO; Logo_silk_ROHS_5x2.8mm
M4: LOGO; Logo_silk_WEEE_3.4x5mm
MH1, MH2, MH3, MH4: SCREWHOLE; MECHANICAL_CLEARANCEHOLE_4_40
R1: 39K; EIA_0402_RES_NOSILK
R2: 1.33K; EIA_0402_RES_NOSILK
R3, R17: 33K; EIA_0402_RES_NOSILK
R4, R18: 8.06K; EIA_0402_RES_NOSILK
R5, R7, R12, R14, R22, R24: 10K; EIA_0402_RES_NOSILK
R6, R19: 470; EIA_0402_RES_NOSILK
R8: LVK24R025DER; OHMITE_LVK24
R9, R20: DNP; EIA_0402_RES_NOSILK
R10, R11: 4.7K; EIA_0402_RES_NOSILK
R13: 1.82K; EIA_0402_RES_NOSILK
R15: LVK25R005FER; OHMITE_LVK25
R16: 470 1/4W; EIA_0603_RES_NOSILK
R21, R23: 0; EIA_0402_RES_NOSILK
TP1, TP2: TESTPOINT; TESTPOINT_SMT_0.5MM
U1: STM32L031-QFN32; QFN_32_0.5MM_5x5MM
U2, U3: AD8218; DFN_8_0.5MM_2x3MM_TALL
U4: TPS7A2533DRVR; DFN_6_0.65MM_2x2MM
U5: AT30TS74_UDFN; DFN_8_0.5MM_2x3MM_TALL
U6: I3A4W008A033V-001-R; MODULE_TDK_I3A4W008A033V
U7: NCP45560; DFN_12_0.5MM_3x3MM
U8: TPS7A2550DRVR; DFN_6_0.65MM_2x2MM

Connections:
/3V3_SB: C3.1, C4.1, C6.1, C7.1, C9.1, C11.1, C15.1, FB2.2, J3.1, J4.1, J5.1 (In), R9.1, R10.1, R11.1, R12.2, R14.2, R22.2, U1.1 (VDD), U1.17 (VDD), U4.1 (OUT), U5.8 (VCC), U7.3 (VCC)
/3V3_SB_PGOOD: R12.1, TP1.1, U4.3 (PG)
/5V0_SB: C18.1, C19.1, C21.1, J12.1 (In), R24.2, U2.2 (VS+), U3.2 (VS+), U8.1 (OUT)
/5V0_SB_PGOOD: R24.1, TP2.1, U8.3 (PG)
/12V0: C17.1, J8.1 (In), J9.1, J9.2, J9.3, R3.2, R16.2, U7.8 (VOUT), U7.9 (VOUT), U7.10 (VOUT), U7.11 (VOUT), U7.12 (VOUT)
/12V0_BLEED: R16.1, U7.7 (BLEED)
/12V0_OK: R14.1, U1.12 (PA6), U6.5 (PGOOD)
/12V0_OUT_EN: J4.5, R7.2, U1.10 (PA4), U7.2 (EN)
/12V0_RAW: FB3.2, J6.1 (In), R15.2 (Vo), R21.1
/12V0_REMOTE: J9.4, R17.2
/12V0_REMOTE_VSENSE: R17.1, R18.2, U1.14 (ADC_IN8)
/12V0_SENSE: R20.2, R21.2, U6.7 (SENSE+)
/12V0_SHIN: C12.1, C13.1, C14.1, R15.4 (Vi), U6.8 (VOUT+)
/12V0_SWIN: C10.1, C20.1, FB3.1, J7.1 (In), R20.1, U4.4 (EN), U4.6 (IN), U7.1 (VIN), U7.PAD (VIN), U8.4 (EN), U8.6 (IN)
/12V0_VSENSE: R3.1, R4.2, U1.15 (ADC_IN9)
/12V_SHUNT_FILT: C23.2, L2.1, U1.13 (ADC_IN7)
/12V_SHUNT_N: R15.1 (Ilo), U3.8 (IN_N)
/12V_SHUNT_P: R15.3 (Ihi), U3.1 (IN_P)
/12V_SHUNT_VOUT: L2.2, U3.5 (OUT)
/48V0: C1.1, C2.1, R1.2, R8.2 (Vo), U6.1 (VIN+)
/48V0_VSENSE: R1.1, R2.2, U1.8 (ADC_IN2)
/48V_CMC: FB1.2, FL1.4
/48V_FUSED: F1.2, FL1.1
/48V_RAW: F1.1, J1.1 (VCC), J1.2 (VCC), J1.3 (VCC)
/48V_SHIN: FB1.1, R8.4 (Vi)
/48V_SHUNT_FILT: C22.2, L1.1, U1.7 (ADC_IN1)
/48V_SHUNT_N: R8.1 (Ilo), U2.8 (IN_N)
/48V_SHUNT_P: R8.3 (Ihi), U2.1 (IN_P)
/48V_SHUNT_VOUT: L1.2, U2.5 (OUT)
/A3V3: C8.1, FB2.1, U1.5 (VDDA)
/BOOT0: R5.1, U1.31 (BOOT0)
/GND: C1.2, C2.2, C3.2, C4.2, C5.2, C6.2, C7.2, C8.2, C9.2, C10.2, C11.2, C12.2, C13.2, C14.2, C15.2, C16.2, C17.2, C18.2, C19.2, C20.2, C21.2, C22.1, C23.1, D1.1 (K), D2.1 (K), FL1.3, J2.3, J3.2, J4.2, J5.2 (Ext), J6.2 (Ext), J7.2 (Ext), J8.2 (Ext), J9.5, J9.6, J9.7, J9.8, J10.1, J11.1, J12.2 (Ext), R2.1, R4.1, R5.2, R7.1, R13.2, R18.1, R23.1, U1.PAD (GND), U2.3 (ENB), U2.4 (GND), U2.7 (REF), U2.PAD (GND), U3.3 (ENB), U3.4 (GND), U3.7 (REF), U3.PAD (GND), U4.5 (GND), U4.PAD (GND), U5.4 (GND), U5.5 (A2), U5.6 (A1), U5.7 (A0), U6.3 (VIN-), U6.4 (VOUT-), U7.4 (GND), U8.5 (GND), U8.PAD (GND)
/GND_RAW: FL1.2, J1.4 (GND), J1.5 (GND), J1.6 (GND)
/I2C_SCL: J4.4, R11.2, U1.32 (I2C1_SCL), U5.2 (SCL)
/I2C_SDA: J4.3, R10.2, U1.30 (I2C1_SDA), U5.1 (SDA)
/LED0: R6.2, U1.21 (PA11)
/LED1: R19.2, U1.22 (PA12)
/LOAD_PGOOD: R22.1, U1.9 (PA3), U7.6 (PG)
/RST_N: C5.1, J3.5, R9.2, U1.4 (NRST)
/SWCLK: J3.3, U1.24 (SWCLK)
/SWDIO: J3.4, U1.23 (SWDIO)
/TEMP_ALERT: U1.11 (PA5), U5.3 (ALERT)
/UART_RX: J2.1, U1.25 (USART2_RX)
/UART_TX: J2.2, U1.29 (PB6)
unnamed: C16.1, U7.5 (SR)
unnamed: D1.2 (A), R6.1
unnamed: D2.2 (A), R19.1
unnamed: R13.1, U6.6 (TRIM)
unnamed: R23.2, U6.2 (ON#)

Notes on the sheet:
PCIe 8 pin compatible pinout but using differently keyed connector due to parts availability issues Remote sense cannot run through load switch but provide monitor feedback through MCU
Negative logic on/off
Power dissipation at full load (6A): * 5.4W in converter module * 80 mW input shunt * 180 mW output shunt * 57 mV input divider * 3.5 mW output divider * 21 mW ferrite * 176 mW output switch * Total 5.9W
80.5 mW at 1.6A in
Cmax = 7.8A / SR SR for 3.3V supply = 13.7 kV/s Target slew of 2.6 kV/sec or less SR = 33 uA / Csr so with 0.015 uF we have 2.2 kV/s
4.9 milliohms DC 176 mW dissipated in switch Also cannot do remote sense through the switch So we'll lose about 30 mV in transit at 6A
Float VS+ to power from shunt common mode 20V/V, 25 mR shunt gives 500 mV/A (minus 80 mV internal offset)
Temperature sensor Address = 8'h90
5.094x division Total dissipation in divider 3.5 mW
0.6 milliohms DC 21.6 mW dissipation, 3.6 mV drop
115 ohm nominal internal bleed resistance Max 400 mW internal dissipation 470 will gives discharge current of 20.5 mA Resistor will dissipate ~200 mW, 48 mW in IC (during bleed)
180 mW at 6A out is 30 mV drop Remote sense will compensate for this
Alternate stuff options depending on if we have stability issues w/ remote sense on far side of the ferrite
30.323x division Total dissipation in divider 57 mW
From datasheet: Vref = 0.6V Vonom = 2.59V F = 36.5K G = 511
Float VS+ to power from shunt common mode 20V/V, 5 mR shunt gives 100 mV/A (minus 80 mV internal offset)
10 milliohms DC at 1.6A, this is 16 mV drop and 25.6 mW dissipation
3.3V standby regulator Thermally limited to 115 mA
PGOOD pinned out in case we can source the -003 option in the future -001 version does not have PGOOD feature
48V DC input filtering and protection
5V standby regulator Thermally limited to 142 mA
TODO: is 2.5A too conservative for input fuse? i3A datasheet calls for 20A...

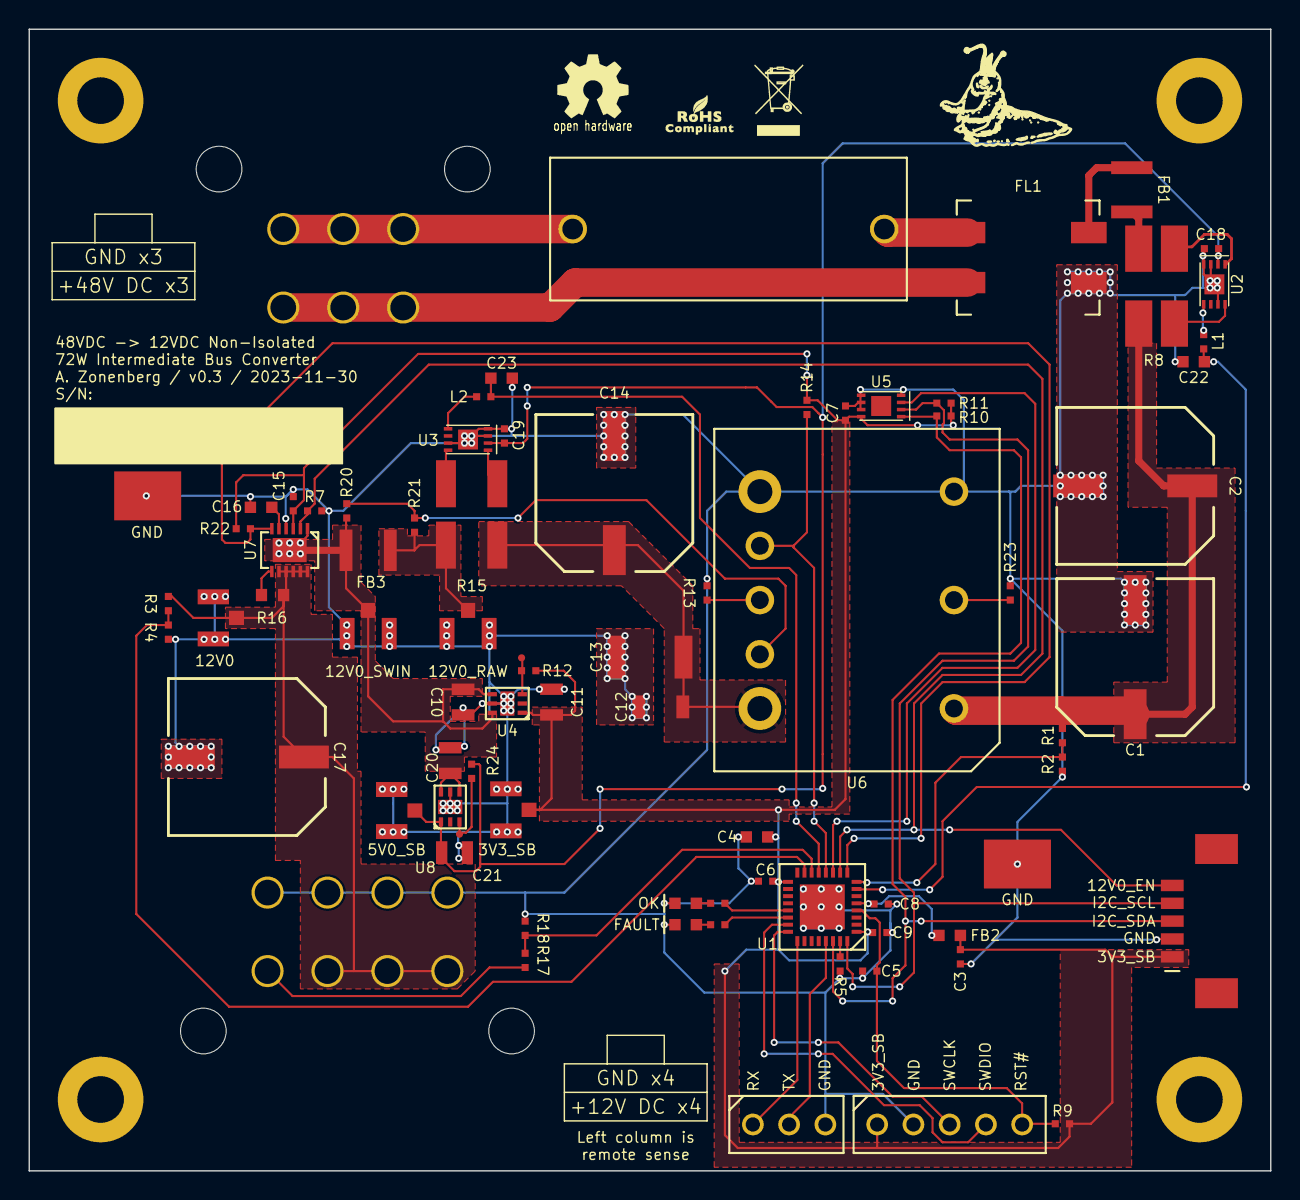
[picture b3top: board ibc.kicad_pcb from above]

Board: 2 copper layers, 87.0 x 80.0 mm, 86 parts (0 on the bottom side), 49 nets.
